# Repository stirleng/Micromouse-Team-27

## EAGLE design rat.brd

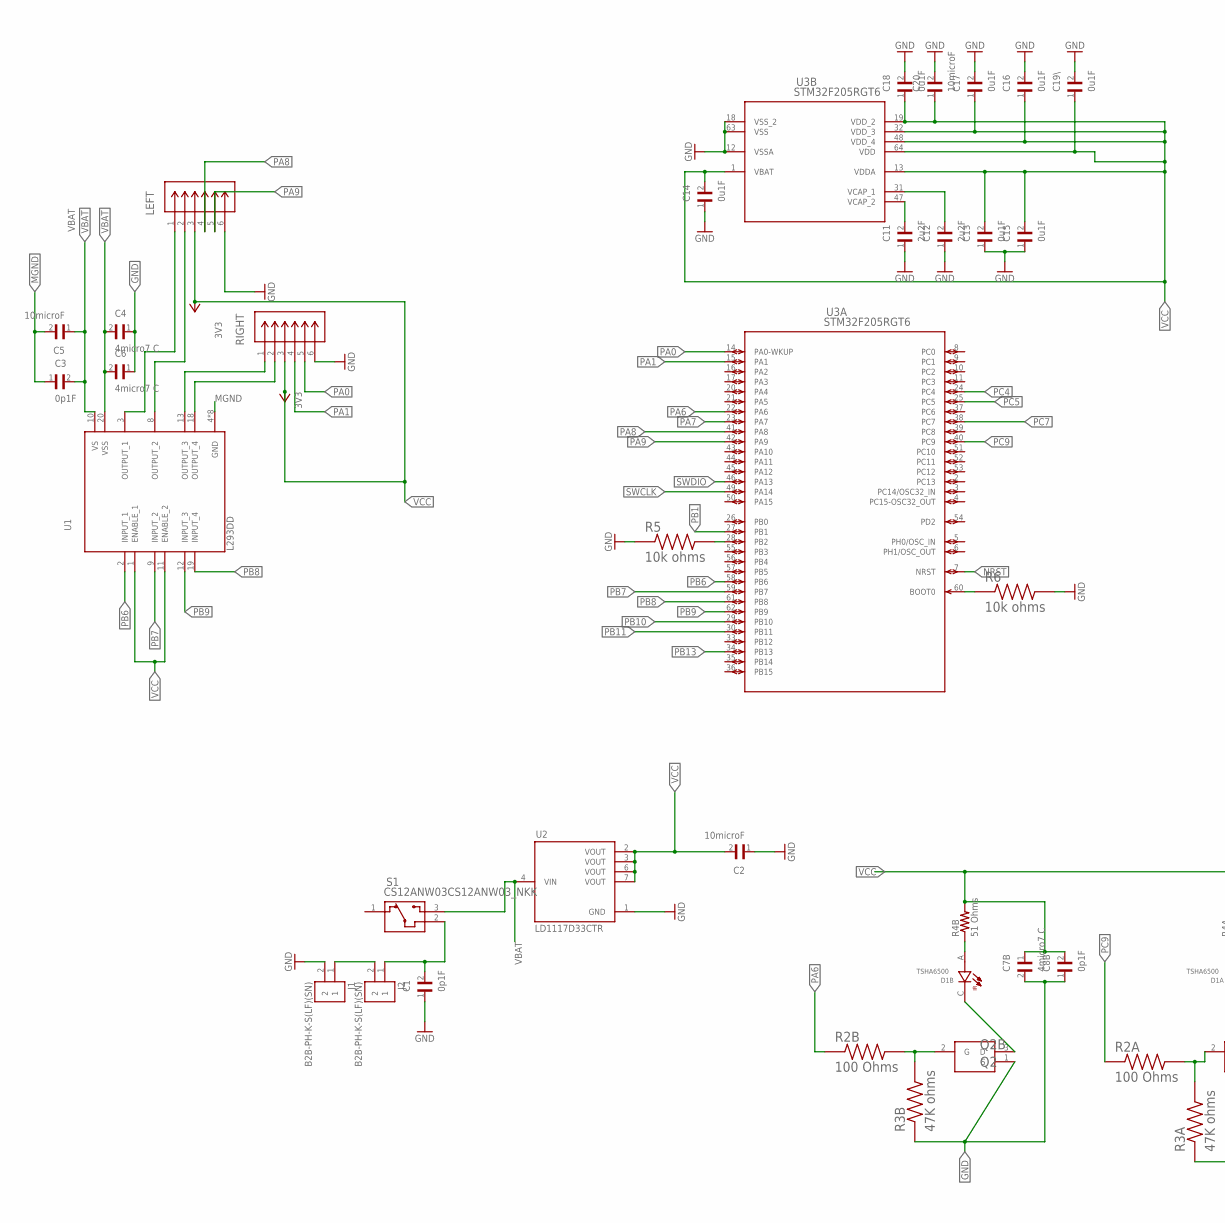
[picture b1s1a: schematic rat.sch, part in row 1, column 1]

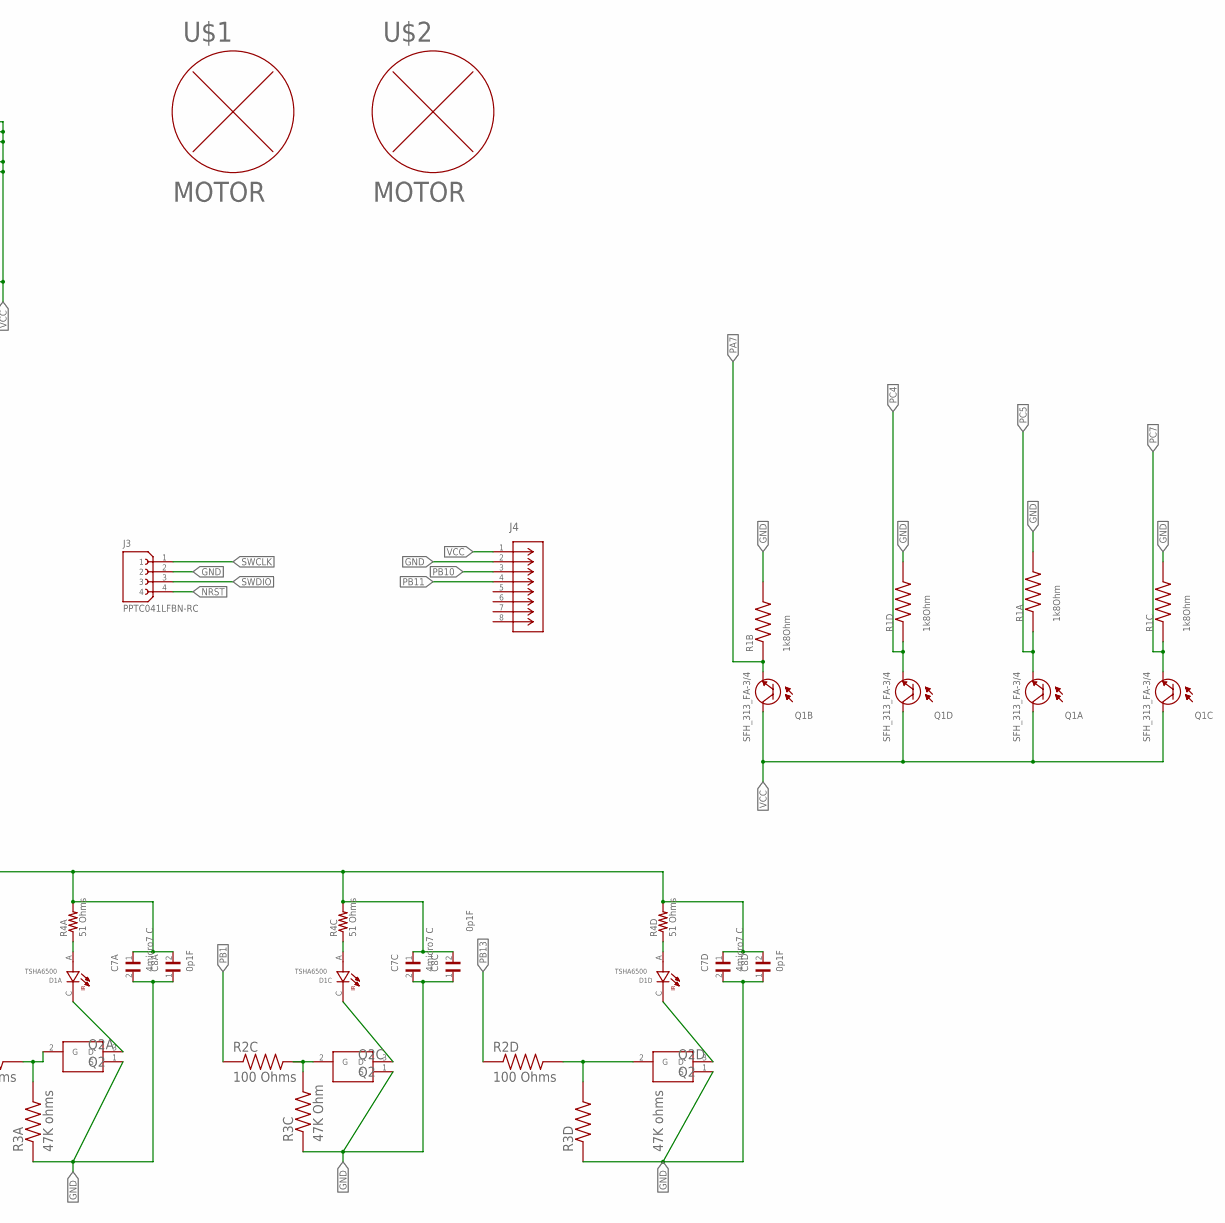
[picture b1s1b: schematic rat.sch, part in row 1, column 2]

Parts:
C1, C3, C8A, C8B, C8C, C8D: 0p1F; CAPC3216X94N
C2, C5, C20: 10microF; CAPC2012X145N
C4, C6, C7A, C7B, C7C, C7D: 4micro7 C; CAPC2012X140N
C11, C12: 2u2F; CAPC3216X140N
C13, C14, C15, C16, C17, C18, C19\: 0u1F; CAPC3216X94N
D1A, D1B, D1C, D1D: TSHA6500; LEDRD254W55D595H900
J1, J2: B2B-PH-K-S(LF)(SN); JST_B2B-PH-K-S(LF)(SN)
J3: PPTC041LFBN-RC; SULLINS_PPTC041LFBN-RC
J4: PPTC081LFBN-RCCONN_PPTC081LFBN-RC_SUL; CONN_PPTC081LFBN-RC_SUL
LEFT: PPTC061LFBN-RCCONN6_061LFBN-RC_SUL; CONN6_061LFBN-RC_SUL
Q1A, Q1B, Q1C, Q1D: SFH_313_FA-3/4; XDCR_SFH_313_FA-3/4
Q2A, Q2B, Q2C, Q2D: Q2; PF5102
R1A, R1B, R1C, R1D: 1k8Ohm; RES_ERJH3EF1801V
R2A, R2B, R2C, R2D: 100 Ohms; RESC2012X50N
R3A, R3B, R3D: 47K ohms; RESC1005X40N
R3C: 47K Ohm; RESC1005X40N
R4A, R4B, R4C, R4D: 51 Ohms; RESC2012X65N
R5, R6: 10k ohms; RESC2012X65N
RIGHT: PPTC061LFBN-RCCONN6_061LFBN-RC_SUL; CONN6_061LFBN-RC_SUL
S1: CS12ANW03CS12ANW03_NKK; CS12ANW03_NKK
U1: L293DD; SOIC127P1032X265-20N
U2: LD1117D33CTR; SOIC127P600X175-8N
U3: STM32F205RGT6; LQFP64-10X10MM
U$1, U$2: MOTOR

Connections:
GND: C1.1, C2.1, C4.1, C6.1, C7A.2, C7B.2, C7C.2, C7D.2, C8A.1, C8B.1, C8C.1, C8D.1, C11.1, C12.1, C13.1, C14.1, C15.1, C16.2, C17.2, C18.2, C19\.2, C20.2, J1.2, J3.2, J4.2, LEFT.6, Q2A.1 (S), Q2B.1 (S), Q2C.1 (S), Q2D.1 (S), R1A.2, R1B.2, R1C.2, R1D.2, R3A.1, R3B.1, R3C.1, R3D.1, R5.1, R6.2, RIGHT.6, U2.1 (GND), U3.12 (VSSA), U3.18 (VSS_2), U3.63 (VSS)
MGND: C3.1, C5.2, U1.4 (GND), U1.5 (GND), U1.6 (GND), U1.7 (GND), U1.14 (GND), U1.15 (GND), U1.16 (GND), U1.17 (GND)
unnamed: J1.1, J2.2
unnamed: C1.2, J2.1, S1.2
unnamed: LEFT.1, U1.3 (OUTPUT_1)
unnamed: LEFT.2, U1.8 (OUTPUT_2)
unnamed: RIGHT.1, U1.13 (OUTPUT_3)
unnamed: RIGHT.2, U1.18 (OUTPUT_4)
unnamed: D1A.C, Q2A.3 (D)
unnamed: Q2A.2 (G), R2A.2, R3A.2
unnamed: D1C.C, Q2C.3 (D)
unnamed: Q2C.2 (G), R2C.2, R3C.2
unnamed: D1A.A, R4A.1
unnamed: D1C.A, R4C.1
unnamed: D1B.C, Q2B.3 (D)
unnamed: Q2B.2 (G), R2B.2, R3B.2
unnamed: D1B.A, R4B.1
unnamed: D1D.C, Q2D.3 (D)
unnamed: Q2D.2 (G), R2D.2, R3D.2
unnamed: D1D.A, R4D.1
unnamed: C11.2, U3.47 (VCAP_2)
unnamed: R6.1, U3.60 (BOOT0)
unnamed: R5.2, U3.28 (PB2)
unnamed: C12.2, U3.31 (VCAP_1)
NRST: J3.4, U3.7 (NRST)
PA0: RIGHT.5, U3.14 (PA0-WKUP)
PA1: RIGHT.4, U3.15 (PA1)
PA6: R2B.1, U3.22 (PA6)
PA7: Q1B.1 (E), R1B.1, U3.23 (PA7)
PA8: LEFT.4, U3.41 (PA8)
PA9: LEFT.5, U3.42 (PA9)
PB1: R2C.1, U3.27 (PB1)
PB6: U1.2 (INPUT_1), U3.58 (PB6)
PB7: U1.9 (INPUT_2), U3.59 (PB7)
PB8: U1.19 (INPUT_4), U3.61 (PB8)
PB9: U1.12 (INPUT_3), U3.62 (PB9)
PB10: J4.3, U3.29 (PB10)
PB11: J4.4, U3.30 (PB11)
PB13: R2D.1, U3.34 (PB13)
PC4: Q1D.1 (E), R1D.1, U3.24 (PC4)
PC5: Q1A.1 (E), R1A.1, U3.25 (PC5)
PC7: Q1C.1 (E), R1C.1, U3.38 (PC7)
PC9: R2A.1, U3.40 (PC9)
SWCLK: J3.1, U3.49 (PA14)
SWDIO: J3.3, U3.46 (PA13)
VBAT: C3.2, C4.2, C5.1, C6.2, S1.3, U1.10 (VS), U1.20 (VSS), U2.4 (VIN)
VCC: C2.2, C7A.1, C7B.1, C7C.1, C7D.1, C8A.2, C8B.2, C8C.2, C8D.2, C13.2, C14.2, C15.2, C16.1, C17.1, C18.1, C19\.1, C20.1, J4.1, LEFT.3, Q1A.2 (C), Q1B.2 (C), Q1C.2 (C), Q1D.2 (C), R4A.2, R4B.2, R4C.2, R4D.2, RIGHT.3, U1.1 (ENABLE_1), U1.11 (ENABLE_2), U2.2 (VOUT), U2.3 (VOUT), U2.6 (VOUT), U2.7 (VOUT), U3.1 (VBAT), U3.13 (VDDA), U3.19 (VDD_2), U3.32 (VDD_3), U3.48 (VDD_4), U3.64 (VDD)

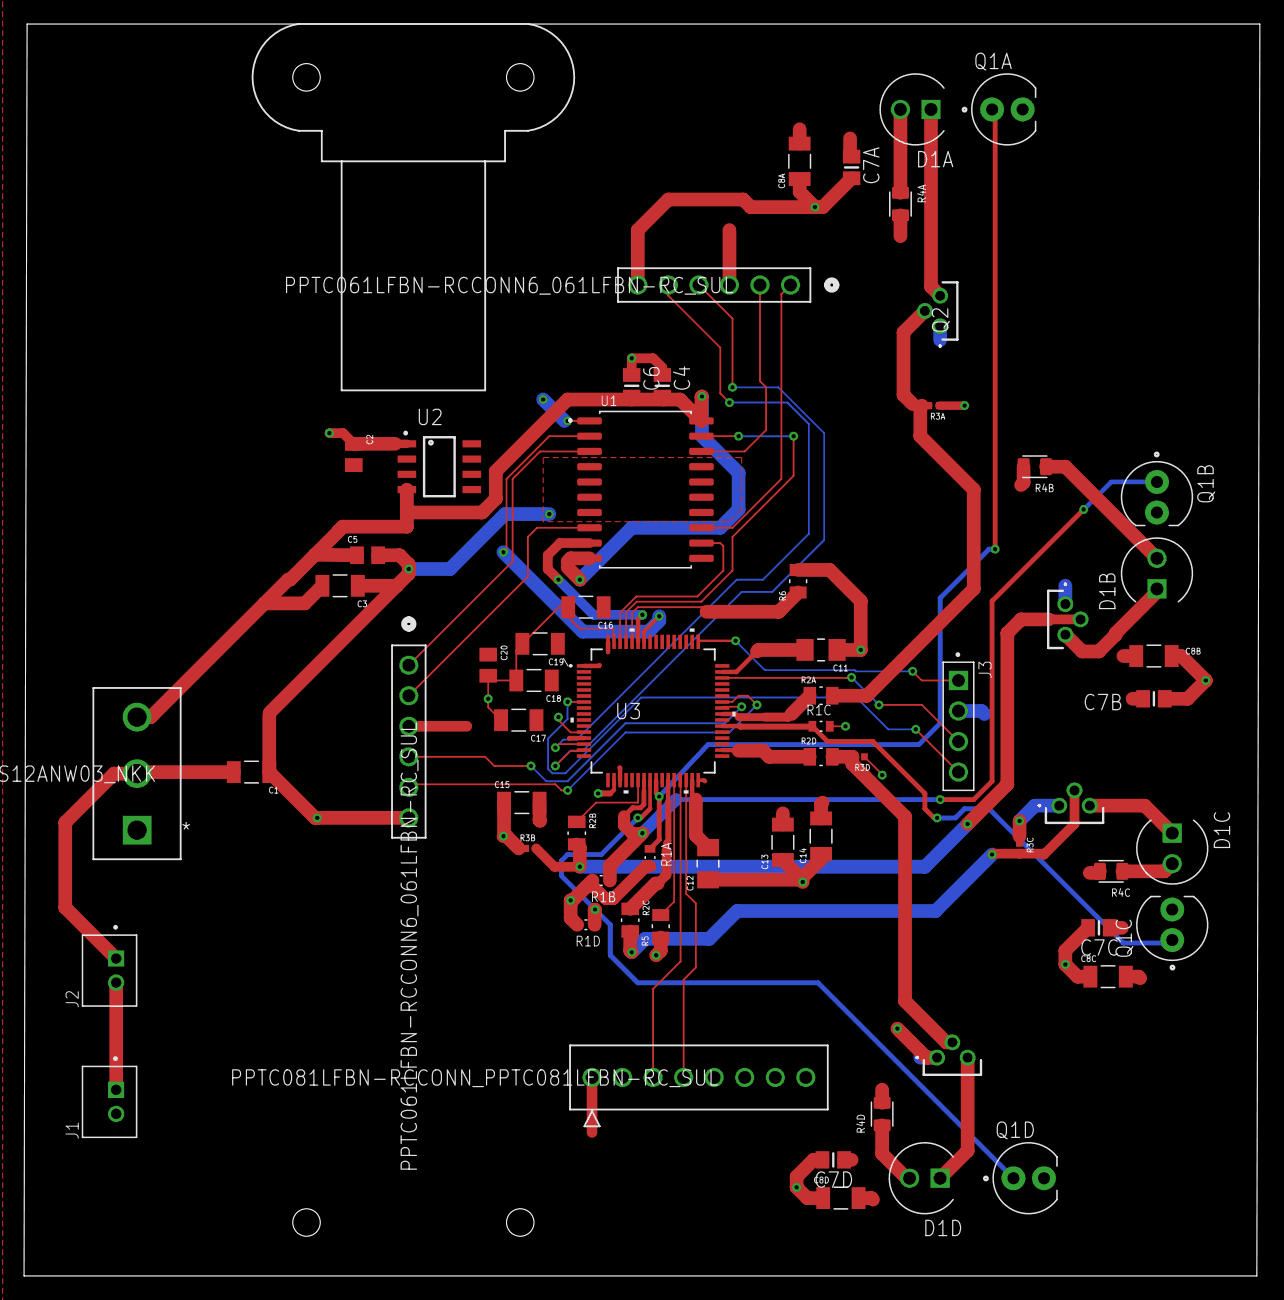
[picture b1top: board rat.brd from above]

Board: 2 copper layers, 102.8 x 104.1 mm, 66 parts (1 on the bottom side), 47 nets.

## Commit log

2022-02-02 Pcb Started
2022-02-03 Some Routing Done
2022-02-06 Airwires eliminated
    Restriction problems still remain; not sure why I can't route under components
2022-02-06 Made Power Signals 45mil Trace
    Still need to make analog signals 15mil trace
2022-02-12 First 6 Review-Required Changes Complete
    Detailed in the "Team 27 PCB Review" Google Doc
2022-02-13 Most of Crucial Changes Made
    Still need to fix rest of trace sizes, make sure all decoupling capacitors are near the correct components, and switch out the incorrect MOSFET for the correct part.
2022-02-14 DRC Cleared
    Necessary changes: make sure decoupling capacitors are near components, adjust power trace sizes
    Suggested Changes: clarify silkscreen, narrow board, round pcb corners

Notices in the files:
parts and their libraries:
COPYRIGHT: Copyright (C) 2022 Ultra Librarian. All rights reserved.
COPYRIGHT: Copyright (C) 2021 Ultra Librarian. All rights reserved.
